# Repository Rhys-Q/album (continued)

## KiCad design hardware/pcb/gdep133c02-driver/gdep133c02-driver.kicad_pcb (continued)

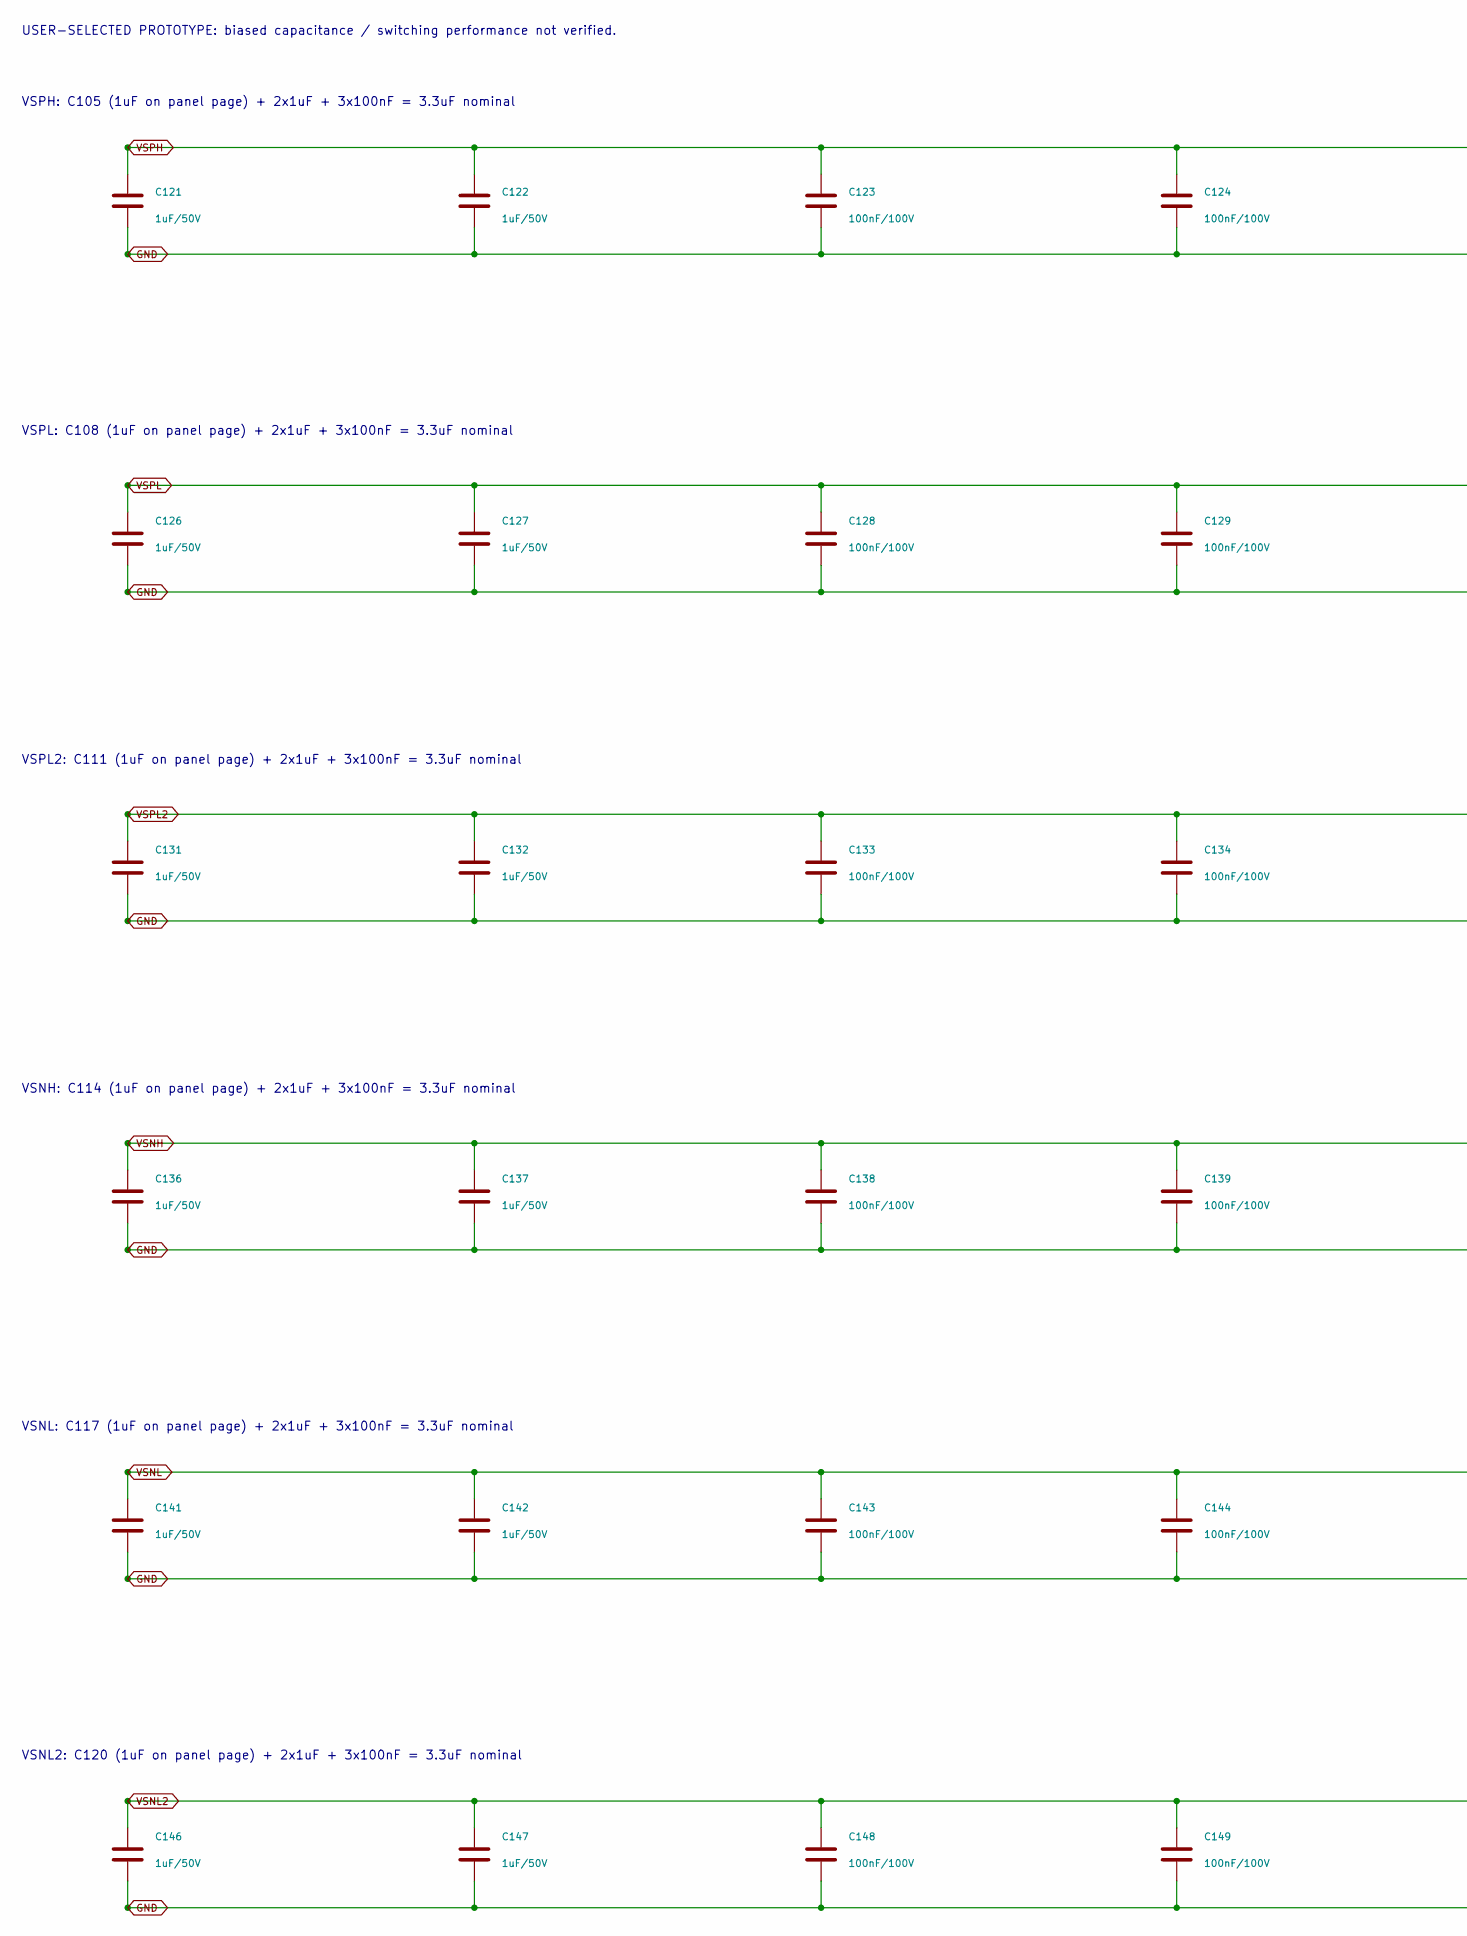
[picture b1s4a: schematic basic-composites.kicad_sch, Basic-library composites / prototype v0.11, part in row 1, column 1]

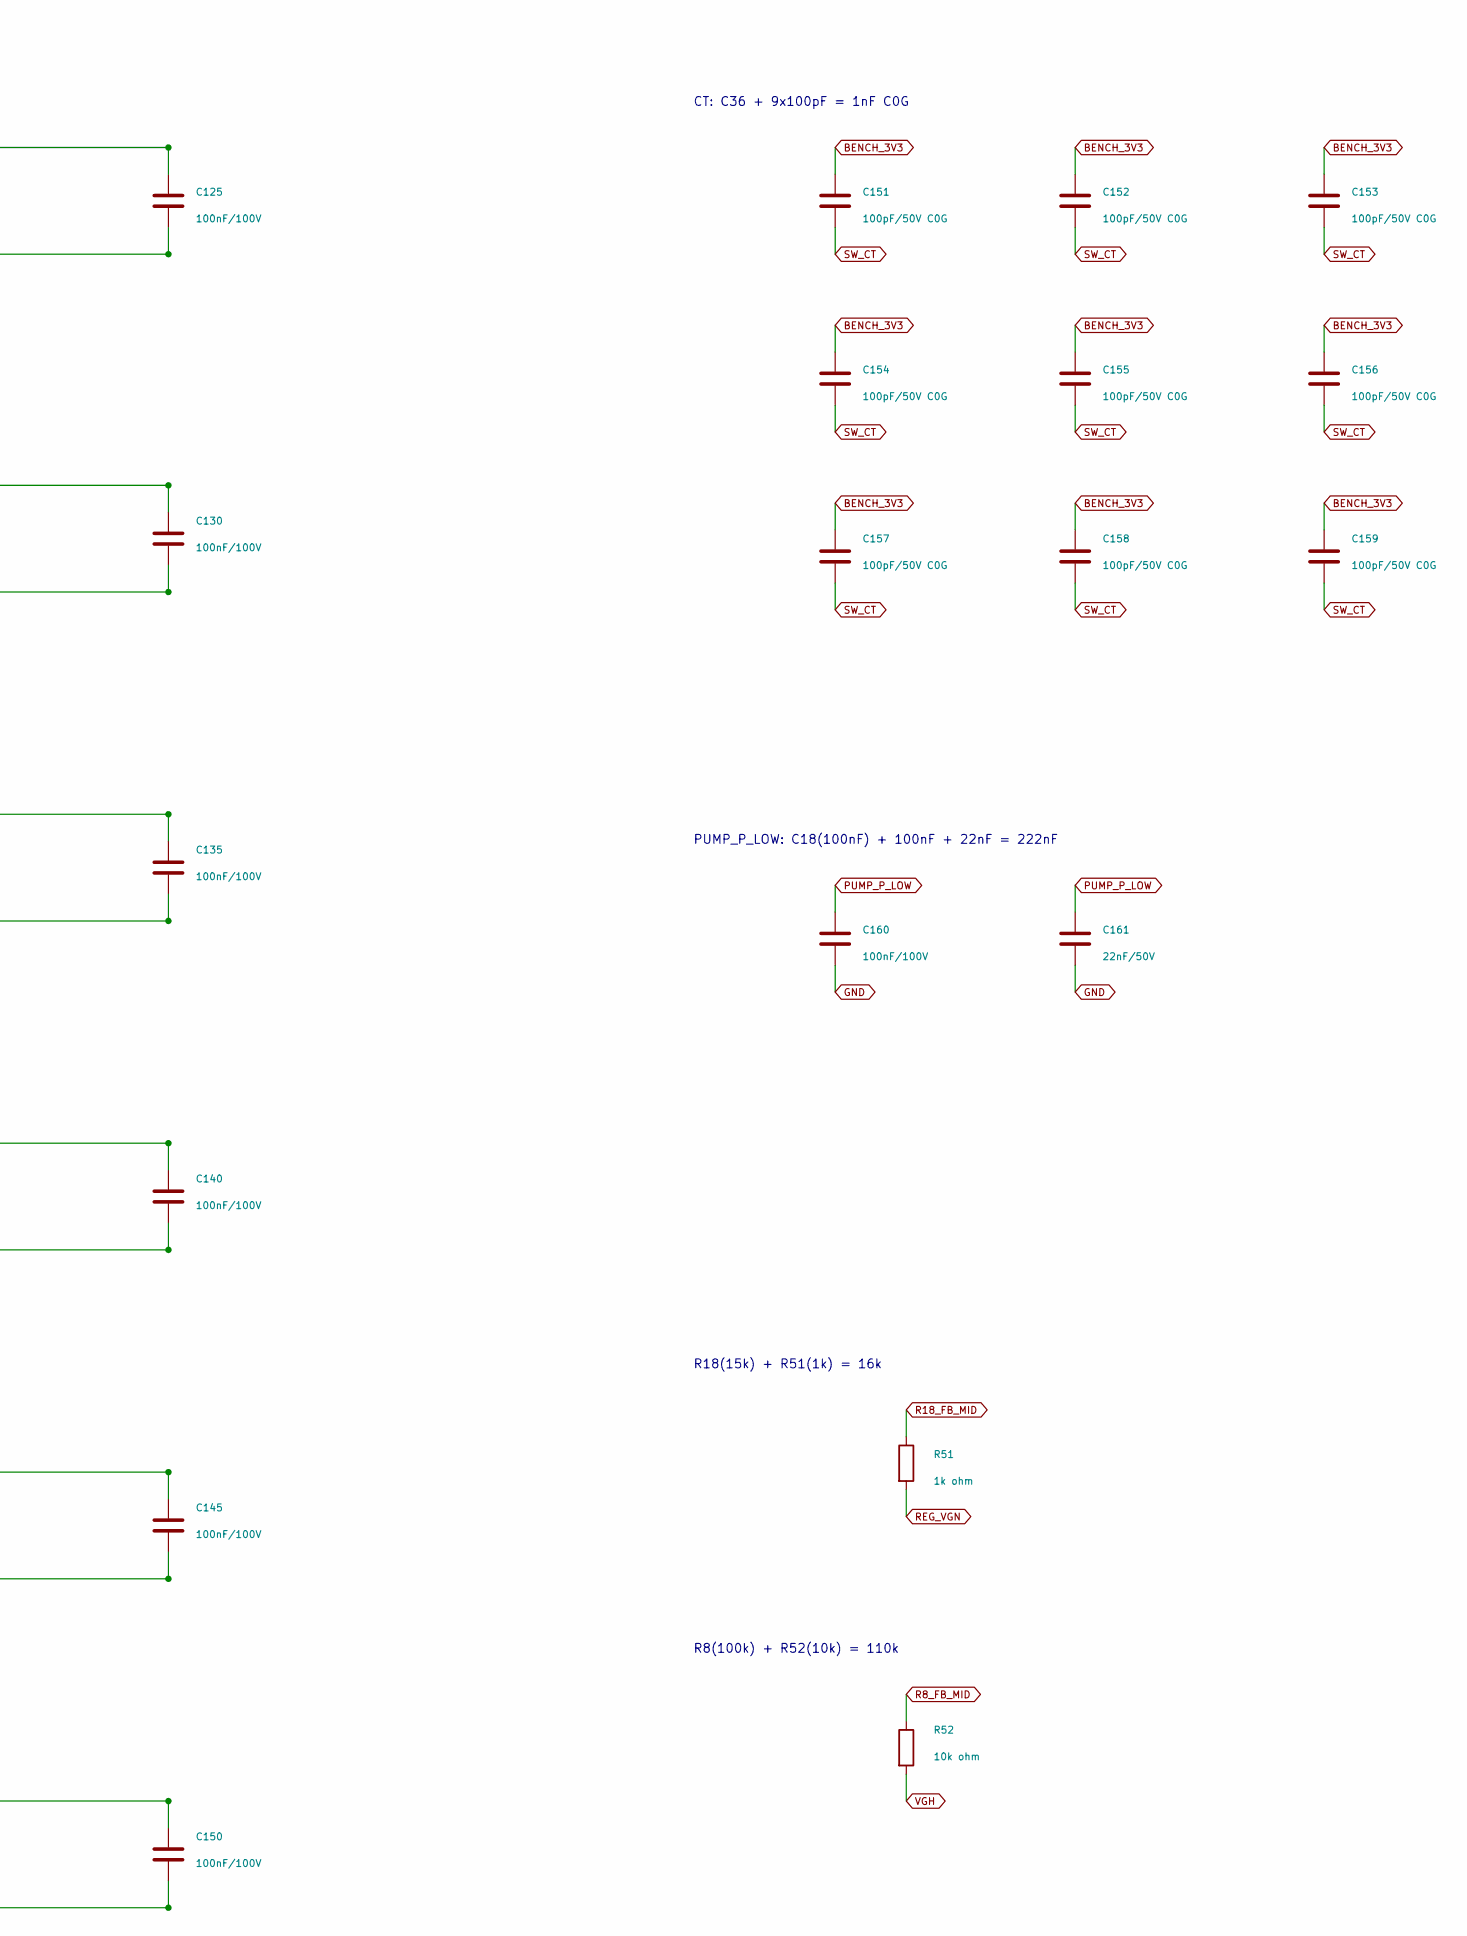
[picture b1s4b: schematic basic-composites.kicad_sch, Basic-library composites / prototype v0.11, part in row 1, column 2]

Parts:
C121, C122, C126, C127, C131, C132, C136, C137, C141, C142, C146, C147: 1uF/50V; C_0805_HandSolder; MPN CL21B105KBFNNNE; LCSC C28323
C123, C124, C125, C128, C129, C130, C133, C134, C135, C138, C139, C140, C143, C144, C145, C148, C149, C150, C160: 100nF/100V; C_0805_HandSolder; MPN CL21B104KCFNNNE; LCSC C28233
C151, C152, C153, C154, C155, C156, C157, C158, C159: 100pF/50V C0G; Capacitor_SMD__C_0603_1608Metric; MPN CL10C101JB8NNNC; LCSC C14858
C161: 22nF/50V; C_0805_HandSolder; MPN CL21B223KBANNNC; LCSC C1729
R51: 1k ohm; R_0805_HandSolder; MPN 0805W8F1001T5E; LCSC C17513
R52: 10k ohm; R_0805_HandSolder; MPN 0805W8F1002T5E; LCSC C17414

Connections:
BENCH_3V3: C151.1, C152.1, C153.1, C154.1, C155.1, C156.1, C157.1, C158.1, C159.1; also elsewhere on the board
GND: C121.2, C122.2, C123.2, C124.2, C125.2, C126.2, C127.2, C128.2, C129.2, C130.2, C131.2, C132.2, C133.2, C134.2, C135.2, C136.2, C137.2, C138.2, C139.2, C140.2, C141.2, C142.2, C143.2, C144.2, C145.2, C146.2, C147.2, C148.2, C149.2, C150.2, C160.2, C161.2; also elsewhere on the board
PUMP_P_LOW: C160.1, C161.1; also elsewhere on the board
R8_FB_MID: R52.1; also elsewhere on the board
R18_FB_MID: R51.1; also elsewhere on the board
REG_VGN: R51.2; also elsewhere on the board
SW_CT: C151.2, C152.2, C153.2, C154.2, C155.2, C156.2, C157.2, C158.2, C159.2; also elsewhere on the board
VGH: R52.2; also elsewhere on the board
VSNH: C136.1, C137.1, C138.1, C139.1, C140.1; also elsewhere on the board
VSNL: C141.1, C142.1, C143.1, C144.1, C145.1; also elsewhere on the board
VSNL2: C146.1, C147.1, C148.1, C149.1, C150.1; also elsewhere on the board
VSPH: C121.1, C122.1, C123.1, C124.1, C125.1; also elsewhere on the board
VSPL: C126.1, C127.1, C128.1, C129.1, C130.1; also elsewhere on the board
VSPL2: C131.1, C132.1, C133.1, C134.1, C135.1; also elsewhere on the board

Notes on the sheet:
USER-SELECTED PROTOTYPE: biased capacitance / switching performance not verified.
VSPH: C105 (1uF on panel page) + 2x1uF + 3x100nF = 3.3uF nominal
VSPL: C108 (1uF on panel page) + 2x1uF + 3x100nF = 3.3uF nominal
VSPL2: C111 (1uF on panel page) + 2x1uF + 3x100nF = 3.3uF nominal
VSNH: C114 (1uF on panel page) + 2x1uF + 3x100nF = 3.3uF nominal
VSNL: C117 (1uF on panel page) + 2x1uF + 3x100nF = 3.3uF nominal
VSNL2: C120 (1uF on panel page) + 2x1uF + 3x100nF = 3.3uF nominal
CT: C36 + 9x100pF = 1nF C0G
PUMP_P_LOW: C18(100nF) + 100nF + 22nF = 222nF
R18(15k) + R51(1k) = 16k
R8(100k) + R52(10k) = 110k

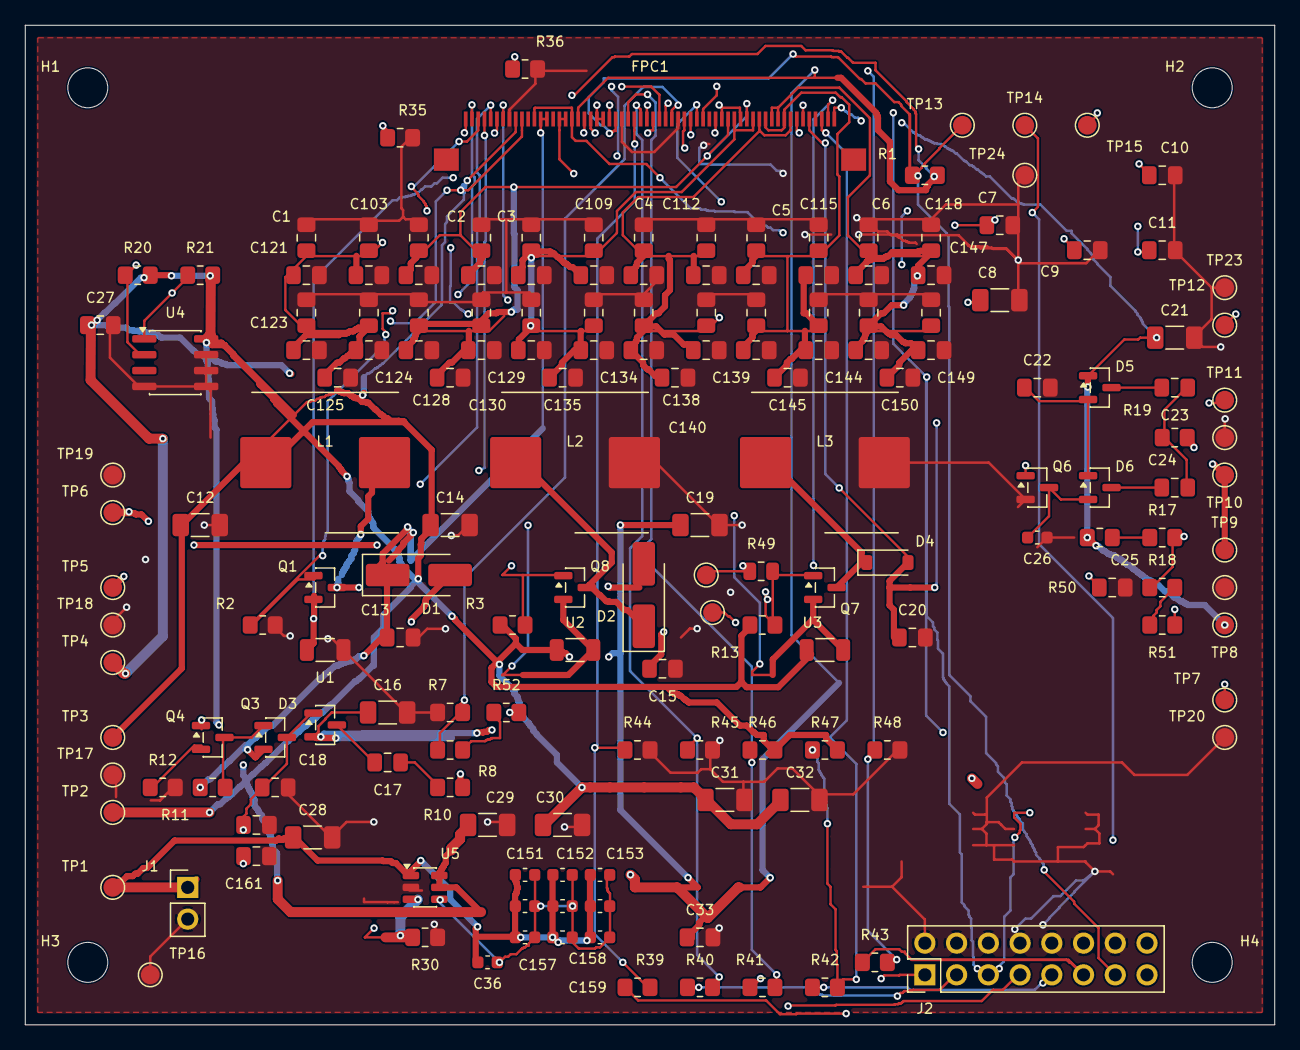
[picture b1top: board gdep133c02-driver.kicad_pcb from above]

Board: 4 copper layers, 100.0 x 80.0 mm, 177 parts (0 on the bottom side), 65 nets.

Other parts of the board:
H1, H2, H3, H4: MountingHole_3.2mm_M3

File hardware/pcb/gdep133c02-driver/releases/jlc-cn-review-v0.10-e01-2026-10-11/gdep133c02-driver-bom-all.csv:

Comment,Designator,Footprint,Quantity,Manufacturer,MPN,LCSC Part #
0 ohm 0805W8F0000T5E,R49,0805,1,UNI-ROYAL,0805W8F0000T5E,C17477
0.2 ohm WSL1206R2000FEA,"U1,U2,U3",1206,3,Vishay,WSL1206R2000FEA,C2073442
1.5k ohm 0805W8F1501T5E,R12,0805,1,UNI-ROYAL,0805W8F1501T5E,C4310
100k ohm 0805W8F1003T5E,"R11,R30,R35,R36,R44,R45,R46,R47,R48",0805,9,UNI-ROYAL,0805W8F1003T5E,C149504
100nF/50V CL21B104KBCNNNC,"C27,C33",0805,2,Samsung,CL21B104KBCNNNC,C1711
100uF/6.3V GRM32ER60J107ME20L,"C31,C32",1210,2,Murata,GRM32ER60J107ME20L,C88154
10uF/50V X5R GRM21BR61H106KE43L,"C1,C103,C104,C106,C107,C109,C110,C112,C113,C115,C116,C118,C119,C13,C15,C2,C20,C3,C4,C5,C6,C7",0805,22,Murata,GRM21BR61H106KE43L,C440198
110k ohm SCR0805F110K,R8,0805,1,VO,SCR0805F110K,C5140228
15uH PCR1040-150-M,"L1,L2,L3",PCR1040 11.5x10.5mm,3,JIERR,PCR1040-150-M,C53896892
16k ohm HP05W3F1602T5E,R18,0805,1,UNI-ROYAL,HP05W3F1602T5E,C2774511
1M ohm 0805W8F1004T5E,"R13,R2,R3",0805,3,UNI-ROYAL,0805W8F1004T5E,C17514
1nF/50V C0G 0805CG102J500NT,C36,0805,1,FH,0805CG102J500NT,C29925
1uF/50V GRM21BR71H105KA12L,"C22,C25",0805,2,Murata,GRM21BR71H105KA12L,C77083
2.2 ohm 0805W8F220KT5E,"R10,R19",0805,2,UNI-ROYAL,0805W8F220KT5E,C17521
200k ohm 0805W8F2003T5E,"R17,R50",0805,2,UNI-ROYAL,0805W8F2003T5E,C17539
220nF/50V GRM21BR71H224KA01L,C18,0805,1,Murata,GRM21BR71H224KA01L,C86042
2k ohm 0805W8F2001T5E,R1,0805,1,UNI-ROYAL,0805W8F2001T5E,C17604
3.3uF/50V GRM32DR71H335KA88L,"C105,C108,C111,C114,C117,C120",1210,6,Murata,GRM32DR71H335KA88L,C397310
33 ohm 0805W8F330JT5E,"R39,R40,R41,R42,R43",0805,5,UNI-ROYAL,0805W8F330JT5E,C17634
3V3 BENCH ONLY TJC8-2.54-2A,J1,PinHeader 1x02 2.54mm,1,DLL,TJC8-2.54-2A,C42410552
4.3k ohm 0805W8F4301T5E,R7,0805,1,UNI-ROYAL,0805W8F4301T5E,C17667
4.7k ohm 0805W8F4701T5E,"R20,R21",0805,2,UNI-ROYAL,0805W8F4701T5E,C17673
4.7uF/50V GRM32ER71H475KA88L,"C12,C14,C16,C19,C21,C28,C29,C30,C8",1210,9,Murata,GRM32ER71H475KA88L,C86052
470nF/50V GRM21BR71H474KA88L,"C10,C11,C17,C23,C24,C9",0805,6,Murata,GRM21BR71H474KA88L,C86043
47nF/50V 0805B473K500NT,C26,0805,1,FH,0805B473K500NT,C1745
B0530W-7-F B0530W-7-F,D4,SOD-123,1,Diodes,B0530W-7-F,C124188
BAT54SLT1G BAT54SLT1G,"D3,D5,D6",SOT-23,3,onsemi,BAT54SLT1G,C19726
DMN3065LW-7 DMN3065LW-7,"Q1,Q4",SOT-323,2,Diodes,DMN3065LW-7,C150506
DMP3068L-7 DMP3068L-7,Q8,SOT-23,1,Diodes,DMP3068L-7,C151010
FPC-05FB-60PH20 FPC-05FB-60PH20,FPC1,FPC 60P 0.5mm,1,Xunpu,FPC-05FB-60PH20,C2856839
HOST DIRECT 3V3 SH-PZ254V-2x8P,J2,PinHeader 2x08 2.54mm,1,SHOU HAN,SH-PZ254V-2x8P,C55629829
MBR230S1F-7 MBR230S1F-7,"D1,D2",SOD-123F,2,Diodes,MBR230S1F-7,C151335
MMBT3904-7-F MMBT3904-7-F,Q6,SOT-23,1,Diodes,MMBT3904-7-F,C94514
MMBT3906-7-F MMBT3906-7-F,Q3,SOT-23,1,Diodes,MMBT3906-7-F,C82762
PJA3433_R1_00001 PJA3433_R1_00001,Q7,SOT-23,1,Panjit,PJA3433_R1_00001,C6628419
TCN75AVOA713 TCN75AVOA713,U4,SOIC-8,1,Microchip,TCN75AVOA713,C144313
TPS22917DBVR TPS22917DBVR,U5,SOT-23-6,1,Texas Instruments,TPS22917DBVR,C2681320

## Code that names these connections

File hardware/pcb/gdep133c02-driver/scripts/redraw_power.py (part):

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
block('1  3.3V input / load switch / supply distribution',7,7,213,48)
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wire('BENCH_3V3',pin('J1',1),pin('R26',1));lab('BENCH_3V3',(19,18))
wire('EPD_VDD',pin('R26',2),pin('R27',1));wire('EPD_VDD',(36,18),pin('C28',1));lab('EPD_VDD',(36,18))
wire('SW_IN',pin('R27',2),pin('U5','A2'));lab('SW_IN',(52,18))
wire('SW_OUT',pin('U5','A1'),pin('R28',1));lab('SW_OUT',(69,18))
wire('EPD_PWR_EN',(31,26),pin('R29',1));lab('EPD_PWR_EN',(31,26))
wire('SW_ON',pin('R29',2),(53,26),(53,20),pin('U5','B2'));wire('SW_ON',(53,26),pin('R30',1));lab('SW_ON',(53,26))
wire('VIN',pin('R28',2),pin('L4',1));wire('VIN',(85,18),pin('C29',1));wire('VIN',(95,18),pin('C30',1));wire('VIN',(100,18),(100,45),pin('L5',1));lab('VIN',(85,18))
wire('EPD_3V3',pin('L4',2),pin('R33',1));wire('EPD_3V3',(121,18),(121,26),pin('R34',1));wire('EPD_3V3',(121,26),pin('C33',1));lab('EPD_3V3',(121,18))
wire('VDD',pin('R33',2),(155,18));lab('VDD',(155,18),180)
wire('VDDIO',pin('R34',2),(155,26));lab('VDDIO',(155,26),180)
wire('AVDD_PRE',pin('L5',2),pin('R31',1));lab('AVDD_PRE',(116,45))
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for r,x,y,a in [('L1',26,66,90),('Q1',38,78,0),('D1',48,66,180),('U1',39,90,0),('R2',24,90,0),('C12',12,90,0),('C13',58,90,0)]:place(r,x,y,a)
wire('AVDD',(12,66),pin('L1',1));wire('AVDD',(12,66),pin('C12',1));lab('AVDD',(12,66))
wire('LX',pin('L1',2),(39,66),pin('D1',2));wire('LX',(39,66),pin('Q1',3));lab('LX',(39,66))
wire('GDRP',(16,78),pin('Q1',1));wire('GDRP',(24,78),pin('R2',1));lab('GDRP',(16,78))
link('RESEP',('Q1',2),('U1',1));lab('RESEP',(39,84))
wire('VDDP',pin('D1',1),(63,66));wire('VDDP',(58,66),pin('C13',1));lab('VDDP',(63,66),180)
wire('GND',(12,97),(58,97))
for r in ['C12','R2','U1','C13']:q=pin(r,2);wire('GND',q,(q[0],97))
gnd(12,97)

for title,off,q,u,l,d,ru,rg,rs,capin,capout,out in [('3  Negative source rail (VDDN)',0,'Q8','U2','L2','D2','R3','R5','R4','C14','C15','VDDN'),('4  VCOM supply branch',74,'Q7','U3','L3','D4','R13','R15','R14','C19','C20','VBB_3P5V')]:
 block(title,76+off,58,76 if off else 68,42)
 for r,x,y,a in [(q,99,78,180),(u,98,69,0),(l,98,89,0),(d,111,84,0),(ru,130,69,0),(rg,111,78,270),(rs,111,73,270),(capin,83,90,0),(capout,135,90,0)]:place(r,x+off,y,a)
 sense='SENSE_N' if not off else 'SENSE_VCOM';gate='GATE_N' if not off else 'GATE_VCOM';sw='SW_N' if not off else 'SW_VCOM';raw='VDDN_RAW' if not off else out
 wire('AVDD',(83+off,64),(130+off,64));wire('AVDD',(83+off,64),pin(capin,1));wire('AVDD',(98+off,64),pin(u,1));wire('AVDD',(130+off,64),pin(ru,1));lab('AVDD',(83+off,64))
 link(sense,(u,2),(q,2));wire(sense,(98+off,73),pin(rs,2));lab(sense,(98+off,73))
 res='RESEN' if not off else 'RESEC';wire(res,pin(rs,1),(120+off,73));lab(res,(120+off,73),180)
 wire(gate,pin(q,1),pin(rg,2));wire(gate,(103+off,78),(103+off,82),(130+off,82),pin(ru,2));lab(gate,(124+off,82))
 gd='GDRN' if not off else 'GDRC';wire(gd,pin(rg,1),(120+off,78));lab(gd,(120+off,78),180)
 link(sw,(q,3),(l,1));wire(sw,(98+off,84),pin(d,1));lab(sw,(98+off,84))
 if not off:
  place('R6',125,84,90);wire(raw,pin(d,2),pin('R6',1));lab(raw,(116,84));wire(out,pin('R6',2),(141,84))
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 for r in [capin,l,capout]:qxy=pin(r,2);wire('GND',qxy,(qxy[0],97))
 gnd(83+off,97)
# Mode-accepted zero-ohm connection, drawn once at the output of the VCOM branch.
place('R16',219,89,90);wire('VBB_3P5V',(215,84),(217.5,84),pin('R16',1));wire('VNCP_3P5V',pin('R16',2),(227,89));lab('VNCP_3P5V',(227,89),180)

block('5  Positive gate charge pump (VGH)',7,104,104,51)
for r,x,y,a in [('Q3',34,121,180),('Q4',47,134,0),('R11',48,113,0),('R12',48,143,0),('D3',67,127,0),('C16',73,143,0),('C17',76,133,90),('C18',33,143,0),('R7',82,146,180),('R8',82,138,180),('R9',89,127,90),('R10',89,133,90)]:place(r,x,y,a)
wire('VDDP',(33,110),(48,110),pin('R11',1));wire('VDDP',(33,110),pin('Q3',2));lab('VDDP',(33,110))
wire('BASE_P',pin('Q3',1),(48,121),pin('Q4',3));wire('BASE_P',pin('R11',2),(48,121));lab('BASE_P',(48,121))
wire('PUMP_P_LOW',pin('Q3',3),(33,127),pin('D3',1));wire('PUMP_P_LOW',(33,127),pin('C18',1));lab('PUMP_P_LOW',(43,127))
link('SOURCE_VGP',('Q4',2),('R12',1));lab('SOURCE_VGP',(48,138))
wire('DRVP',(39,134),pin('Q4',1));lab('DRVP',(39,134))
wire('PUMP_P_MID',pin('D3',3),(67,133),pin('C17',1));lab('PUMP_P_MID',(67,133))
link('PUMP_P_AC',('C17',2),('R10',1));lab('PUMP_P_AC',(80,133))
wire('LX',pin('R10',2),(105,133));lab('LX',(105,133),180)
link('VGH_RAW',('D3',2),('R9',1));wire('VGH_RAW',(73,127),pin('C16',1));wire('VGH_RAW',(82,127),pin('R8',2));lab('VGH_RAW',(73,127))
wire('VGH',pin('R9',2),(105,127));lab('VGH',(105,127),180)
link('FBP',('R8',1),('R7',2));wire('FBP',(82,142),(98,142));lab('FBP',(98,142),180)
wire('GND',(33,151),(82,151))
for r,n in [('C18',2),('R12',2),('C16',2),('R7',1)]:qxy=pin(r,n);wire('GND',qxy,(qxy[0],151))
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
block('6  Negative gate charge pump (VGL)',117,104,107,51)
for r,x,y,a in [('Q6',182,134,0),('D5',141,119,0),('D6',141,134,0),('C21',122,128,0),('C22',151,143,0),('C23',161,123,90),('C24',161,138,90),('C25',138,146,0),('C26',195,143,0),('R17',128,138,0),('R18',128,146,0),('R19',182,123,90)]:place(r,x,y,a)
wire('VGL',(120,119),pin('D5',1));wire('VGL',(122,119),pin('C21',1));wire('VGL',(128,119),pin('R17',1));lab('VGL',(120,119))
wire('PUMP_N_MID',pin('D5',2),(151,119),(151,126),(135,126),(135,134),pin('D6',1));wire('PUMP_N_MID',(151,126),pin('C22',1));lab('PUMP_N_MID',(151,126))
wire('PUMP_N_UP',pin('D5',3),(141,123),pin('C23',1));lab('PUMP_N_UP',(145,123))
wire('PUMP_N_DOWN',pin('D6',3),(141,138),pin('C24',1));lab('PUMP_N_DOWN',(145,138))
wire('PUMP_N_AC',pin('C23',2),(169,123),pin('R19',1));wire('PUMP_N_AC',pin('C24',2),(169,138),(169,123));lab('PUMP_N_AC',(169,123))
wire('LX',pin('R19',2),(210,123));lab('LX',(210,123),180)
wire('PUMP_N_LOW',pin('D6',2),(173,134),(173,130),(195,130),pin('C26',1));wire('PUMP_N_LOW',(183,130),pin('Q6',3));lab('PUMP_N_LOW',(186,130))
wire('DRVN',pin('Q6',1),(177,134),(177,140));lab('DRVN',(177,140))
link('FBN',('R17',2),('R18',1));lab('FBN',(128,141))
wire('REG_VGN',pin('R18',2),(132,147.5),(132,141),(138,141),pin('C25',1));lab('REG_VGN',(138,141))
wire('GND',(122,151),(195,151))
for r,n in [('C21',2),('C22',2),('C25',2),('C26',2),('Q6',2)]:qxy=pin(r,n);wire('GND',qxy,(qxy[0],151))
gnd(195,151)
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
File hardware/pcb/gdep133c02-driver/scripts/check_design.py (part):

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 assert footprint_links.get(ref)==expected, ('PCB symbol link incompatible with KiCad',ref,footprint_links.get(ref),expected)
pads=json.loads((ROOT/'reports/pads.json').read_text());actual={(p['ref'],p['pin']):p['netname'] for p in pads if p['net'] and not p['netname'].startswith('unconnected-')}
assert actual==want,('PCB pads differ from schematic',set(actual.items())^set(want.items()))
for pin,net in [('22','EPD_3V3'),('23','EPD_3V3'),('26','GND'),('41','VBB_3P5V'),('56','VBB_3P5V')]:assert parts['FPC1']['pins'][pin]==net
for pin in ['11','15','40','57']:assert parts['FPC1']['pins'][pin] is None
for ref in ['U1','U2','U3']:assert parts[ref]['value']=='0.2 ohm'
assert parts['U4']['pins']['8']=='EPD_3V3' and parts['U4']['pins']['3'] is None
assert set(parts['R1']['pins'].values())=={'BUSY_N','EPD_3V3'}
assert parts['J2']['pins']['16'] is None
assert parts['J2']['pins']['5']=='SI1' and parts['J2']['pins']['13']=='BUSY_N'
assert parts['U5']['mpn']=='TPS22917DBVR'
assert parts['U5']['pins']=={'1':'BENCH_3V3','2':'GND','3':'EPD_PWR_EN','4':'SW_CT','5':'EPD_3V3','6':'EPD_3V3'}
assert set(parts['C36']['pins'].values())=={'SW_CT','BENCH_3V3'}
ct_refs=['C36']+['C'+str(i) for i in range(151,160)]
assert len(ct_refs)==10
for ref in ct_refs:
 assert parts[ref]['mpn']=='CL10C101JB8NNNC' and parts[ref]['lcsc']=='C14858'
 assert parts[ref]['value']=='100pF/50V C0G' and set(parts[ref]['pins'].values())=={'SW_CT','BENCH_3V3'}
assert parts['C28']['mpn']==parts['C29']['mpn']=='1206B475K500NT'
assert parts['C28']['value']==parts['C29']['value']=='4.7uF/50V'
assert parts['C28']['fp']==parts['C29']['fp']=='Driver:C_1206_HandSolder'
assert parts['C28']['pins']=={'1':'BENCH_3V3','2':'GND'}
for ref in ['L1','L2','L3']:
 assert parts[ref]['mpn']=='PCR1040-150-M' and parts[ref]['fp']=='Driver:L_JIERR_PCR1040'
# Preserve electrical constraints independent of purchasing changes.
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  assert fields.get(key)==parts[ref][prop],('Schematic procurement field mismatch',ref,key)
assert parts['R7']['value']=='4.3k ohm' and parts['R8']['value']=='100k ohm' and parts['R52']['value']=='10k ohm'
assert parts['R18']['value']=='15k ohm' and parts['R51']['value']=='1k ohm'
assert parts['R8']['pins']=={'1':'FBP','2':'R8_FB_MID'}
assert parts['R52']['pins']=={'1':'R8_FB_MID','2':'VGH'}
assert parts['R18']['pins']=={'1':'FBN','2':'R18_FB_MID'}
assert parts['R51']['pins']=={'1':'R18_FB_MID','2':'REG_VGN'}
assert parts['C18']['value']==parts['C160']['value']=='100nF/100V'
assert parts['C161']['value']=='22nF/50V'
assert parts['C18']['pins']==parts['C160']['pins']==parts['C161']['pins']
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removed={'C34','C35','Q9','Q10','R14','R15','R16','R22','R23','R24','R25','R26','R27','R28','R29','R31','R32','R33','R34','R37','R38','R4','R5','R6','R9','U6','U7'}
assert not (set(removed)|{'L4','L5'}).intersection(parts)
assert not {'VIN','AVDD'}.intersection(want.values())
assert parts['R49']['pins']=={'1':'GDRC','2':'Q7_GATE'}
assert parts['R49']['value']=='0 ohm' and 'R_0805_' in parts['R49']['fp'] and not parts['R49']['dnp']
assert parts['Q7']['pins']['1']=='Q7_GATE' and parts['R13']['pins']['2']=='Q7_GATE'
assert parts['TP25']['pins']=={'1':'GDRC'} and parts['TP26']['pins']=={'1':'Q7_GATE'}
assert parts['TP25']['dnp'] and parts['TP26']['dnp']
assert [z['ref'] for z in parts.values() if {'GDRC','Q7_GATE'} <= set(z['pins'].values())]==['R49']
for ref in ['C29','C30','C31','C32','C33']:
 assert set(parts[ref]['pins'].values())=={'EPD_3V3','GND'}
assert sum(not z['dnp'] for z in parts.values())==data['assembled_components']
assert len(want)==sum(bool(v) for z in data['parts'] for v in z['pins'].values())
assert parts['R17']['value']==parts['R50']['value']=='200k ohm'
assert parts['R17']['pins']=={'1':'VGL_FB_MID','2':'FBN'}
assert parts['R50']['pins']=={'1':'VGL','2':'VGL_FB_MID'}
for ref,host,screen in [('R39','HOST_SCLK','SCLK'),('R40','HOST_MOSI','SI0'),('R41','HOST_CS_M_N','CS_M_N'),('R42','HOST_CS_S_N','CS_S_N'),('R43','HOST_RES_N','RES_N')]:
 assert parts[ref]['pins']=={'1':host,'2':screen}
# Footprints must resolve locally, with no personal-directory model dependencies.
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
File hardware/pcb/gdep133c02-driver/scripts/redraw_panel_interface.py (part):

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p.wire('VDD',(108,30),(108,35));p.lab('VDD',(108,30),180)
for net,y in [('BS0',30),('BS1',35)]:p.lab(net,(82,y))
for n in [24,25,27,28,29,30,31,32,58]:q=p.pin('FPC1',n);net=data['FPC1']['pins'][str(n)];p.wire(net,q,(120,q[1]));p.lab(net,(120,q[1]),180)
p.place('R1',112,42,180);p.wire('BUSY_N',p.pin('R1',1),(112,47));p.wire('VDDIO',p.pin('R1',2),(112,37));p.lab('VDDIO',(112,37),180)
for r,n,x in [('R35',31,85),('R36',32,116)]:
 p.place(r,x,88);net=data[r]['pins']['1'];p.wire(net,(x,p.pin('FPC1',n)[1]),p.pin(r,1));p.wire('GND',p.pin(r,2),(x,94))
p.wire('GND',(85,94),(116,94));p.gnd(116,94)
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for r,net,x,y in [('R20','TSCL',100,15.5),('R21','TSDA',125,19.5)]:
 # Pullup pin1 signal, pin2 supply.
 p.place(r,x,y,180)
 p.wire(net,p.pin(r,1),(x,17 if net=='TSCL' else 21));q=p.pin(r,2);p.wire('EPD_3V3',q,(x,7))
p.wire('EPD_3V3',(100,7),(206,7));p.wire('EPD_3V3',(154,7),p.pin('U4',8));p.lab('EPD_3V3',(206,7),180)
p.place('C27',202,38);p.wire('EPD_3V3',(202,7),p.pin('C27',1));p.wire('GND',p.pin('C27',2),(202,49))
for n in [4,5,6,7]:q=p.pin('U4',n);p.wire('GND',q,(q[0],49))
p.wire('GND',(149,49),(202,49));p.gnd(154,49)
p.place('R22',180,18,180);p.wire('EPD_3V3',(180,7),p.pin('R22',2));p.wire('ALERT_N',p.pin('R22',1),(180,25))
p.place('R23',190,34);p.wire('ALERT_N',p.pin('U4',3),(190,25),p.pin('R23',1));p.lab('ALERT_N',(185,25),180);p.wire('GND',p.pin('R23',2),(190,49))
p.note('R23 DNP: alert output is not strapped to ground.',140,55,.9)
# Common-electrode output bypass and six capacitor banks, directly paired at connector.
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
s.block('2  Host to panel - buffered SPI / default levels',58,5,100,141)
rows=[27,39,51,63,75,87,95,103];buffer('U6',94,rows,[111,115],124)
for r,pin_in,pin_out,host,raw,out,y in [('R39',2,18,'HOST_SCLK','BUF_SCLK','SCLK',27),('R40',4,16,'HOST_MOSI','BUF_MOSI','SI0',39),('R41',6,14,'HOST_CS_M_N','BUF_CS_M_N','CS_M_N',51),('R42',8,12,'HOST_CS_S_N','BUF_CS_S_N','CS_S_N',63),('R43',11,9,'HOST_RES_N','BUF_RES_N','RES_N',75)]:
 s.wire(host,(65,y),s.pin('U6',pin_in));s.lab(host,(65,y));s.place(r,122,y,90);s.wire(raw,s.pin('U6',pin_out),s.pin(r,1));s.lab(raw,(113,y));s.wire(out,s.pin(r,2),(153,y));s.lab(out,(153,y),180)
for r,net,y in [('R44','SCLK',27),('R45','SI0',39),('R46','CS_M_N',51),('R47','CS_S_N',63),('R48','RES_N',75)]:
 pullup=r in ['R46','R47'];x=146 if pullup else 140;s.place(r,x,y-4 if pullup else y+4,180 if pullup else 0);s.wire(net,(x,y),s.pin(r,1));q=s.pin(r,2)
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s.wire('GND',(76,87),(76,106));s.gnd(76,106)
for n in [1,19]:q=s.pin('U6',n);s.wire('OE_PANEL_N',q,(74,q[1]))
s.wire('OE_PANEL_N',(74,111),(74,134));s.wire('OE_PANEL_N',(74,111),(64,111));s.lab('OE_PANEL_N',(64,111))
s.place('Q9',73,136);s.wire('OE_PANEL_N',(74,134),s.pin('Q9',3));s.wire('GND',s.pin('Q9',2),(74,142));s.gnd(74,142);s.wire('EPD_PWR_EN',(61,136),s.pin('Q9',1));s.lab('EPD_PWR_EN',(61,136))
s.place('R37',62,124,180);s.wire('OE_PANEL_N',s.pin('R37',1),(62,130),(74,130));s.wire('EPD_3V3',s.pin('R37',2),(62,119));s.lab('EPD_3V3',(62,119))
s.wire('GND',s.pin('U6',10),(94,128));s.gnd(94,128)
s.place('C34',112,12);s.wire('EPD_3V3',(94,8),(112,8),s.pin('C34',1));s.wire('EPD_3V3',(94,8),s.pin('U6',20));s.lab('EPD_3V3',(94,8));s.wire('GND',s.pin('C34',2),(112,17));s.gnd(112,17)
s.note('EPD_PWR_EN high: Q9 pulls both OE inputs low.',84,140,.85)

s.block('3  Panel to host - BUSY / MISO buffer',162,5,68,141)
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s.wire('GND',(173,51),(173,114));s.gnd(173,114)
for n in [1,19]:q=s.pin('U7',n);s.wire('OE_HOST_N',q,(176,q[1]))
s.wire('OE_HOST_N',(176,119),(176,134));s.lab('OE_HOST_N',(176,119))
s.place('Q10',175,136);s.wire('OE_HOST_N',(176,134),s.pin('Q10',3));s.wire('GND',s.pin('Q10',2),(176,142));s.gnd(176,142);s.wire('EPD_PWR_EN',(164,136),s.pin('Q10',1));s.lab('EPD_PWR_EN',(164,136))
s.place('R38',165,124,180);s.wire('OE_HOST_N',s.pin('R38',1),(165,130),(176,130));s.wire('HOST_3V3',s.pin('R38',2),(165,119));s.lab('HOST_3V3',(165,119))
s.wire('GND',s.pin('U7',10),(194,138));s.gnd(194,138)
s.place('C35',212,12);s.wire('HOST_3V3',(194,8),(212,8),s.pin('C35',1));s.wire('HOST_3V3',(194,8),s.pin('U7',20));s.lab('HOST_3V3',(194,8));s.wire('GND',s.pin('C35',2),(212,17));s.gnd(212,17)
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
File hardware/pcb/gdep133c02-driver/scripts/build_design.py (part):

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def c(n,val,a,b,xy,group='power',fp=CFP,mpn='',angle=0):
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# External power (no regulator, battery, USB, or MCU on this prototype).
add('J1','3V3 BENCH ONLY',{1:'BENCH_3V3',2:'GND'},'Connector_PinHeader_2.54mm:PinHeader_1x02_P2.54mm_Vertical',(13,69),'entry',mpn='TSW-102-07-G-S',vendor='Samtec')
r(26,'0','BENCH_3V3','EPD_VDD',(20,69),'entry',fp='Resistor_SMD:R_1206_3216Metric')
c(28,'2.2uF/50V','EPD_VDD','GND',(23,65),'entry')
r(27,'0','EPD_VDD','SW_IN',(27,69),'entry',fp='Resistor_SMD:R_1206_3216Metric')
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    add('U'+str(n),'0.2 ohm',{1:a,2:b},'Resistor_SMD:R_1206_3216Metric',xy,'converters',mpn='WSL1206R2000FEA',vendor='Vishay')
r(2,'1M','GDRP','GND',(19,48),'converters');r(3,'1M','AVDD','GATE_N',(39,48),'converters');r(13,'1M','AVDD','GATE_VCOM',(59,48),'converters')
for n,a,b,xy in [(4,'RESEN','SENSE_N',(39,52)),(5,'GDRN','GATE_N',(39,44)),(6,'VDDN_RAW','VDDN',(50,45)),(14,'RESEC','SENSE_VCOM',(59,52)),(15,'GDRC','GATE_VCOM',(59,44)),(16,'VBB_3P5V','VNCP_3P5V',(70,45))]:r(n,'0',a,b,xy,'converters')
for ref,val,pins,xy,fp in [('D1','MBR230S1F-7',{1:'VDDP',2:'LX'},(29,44),'Diode_SMD:D_SOD-123F'),('D2','MBR230S1F-7',{1:'SW_N',2:'VDDN_RAW'},(49,40),'Diode_SMD:D_SOD-123F'),('D4','B0530W-7-F',{1:'SW_VCOM',2:'VBB_3P5V'},(69,40),'Diode_SMD:D_SOD-123')]:
    add(ref,val,pins,fp,xy,'converters',vendor='Diodes',names={'1':'K','2':'A'})
for n,val,a,xy in [(12,'4.7uF/50V','AVDD',(17,36)),(13,'10uF/50V','VDDP',(30,49)),(14,'4.7uF/50V','AVDD',(37,36)),(15,'10uF/50V','VDDN',(51,49)),(19,'4.7uF/50V','AVDD',(57,36)),(20,'10uF/50V','VBB_3P5V',(71,49))]:c(n,val,a,'GND',xy,'converters')
# Positive gate-voltage pump; BAT54S pin1=A1, pin2=K2, pin3=K1/A2.
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orig=list(csv.DictReader((ROOT.parents[1]/'reference/gdep133c02/pin-map.csv').open()))
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# Exposed current-sense pin RESEP is a panel input, coupled to Q1 source.
# Reference has no discrete zero-ohm between RESEP and Q1 source.
for p in parts:
    if p['ref']=='Q1':p['pins']['2']='RESEP'
    if p['ref']=='U1':p['pins']['1']='RESEP'
# Test pads along board sides; voltage names, no guessed source-rail setpoints.
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    add('TP'+str(i),net,{1:net},'TestPoint:TestPoint_Pad_D1.5mm',xy,'test',mpn='PCB test pad',vendor='PCB',dnp=True)
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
